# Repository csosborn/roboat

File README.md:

# Roboat!

An autonomous, solar-powered boat. An RP2040 microcontroller handles power monitoring and control and supervises a Raspberry Pi, which provides data storage, navigation, planning, and communications.

## Design documents

- [Compute.md](Compute.md): compute architecture and the power-management state machine
- [PowerSystem.md](PowerSystem.md): battery, charge controller, and solar array selection
- [SolarArrayTrade.md](SolarArrayTrade.md): solar array trade study

## Repository layout

| Path | Contents |
| --- | --- |
| `src/micro/` | MicroPython code for the RP2040 Feather (power FSM, Victron MPPT, INA260, Pi link) |
| `src/pi/` | Raspberry Pi monitor service, TIG stack (Telegraf/InfluxDB/Grafana), and systemd units; see [setup notes](src/pi/TIG/setup.md) |
| `src/build-tools/` | Docker container for building custom MicroPython firmware |
| `printed_parts/` | STL files for 3D-printed parts |
| `take1/` | The original Arduino/Eagle-based attempt, kept for reference |

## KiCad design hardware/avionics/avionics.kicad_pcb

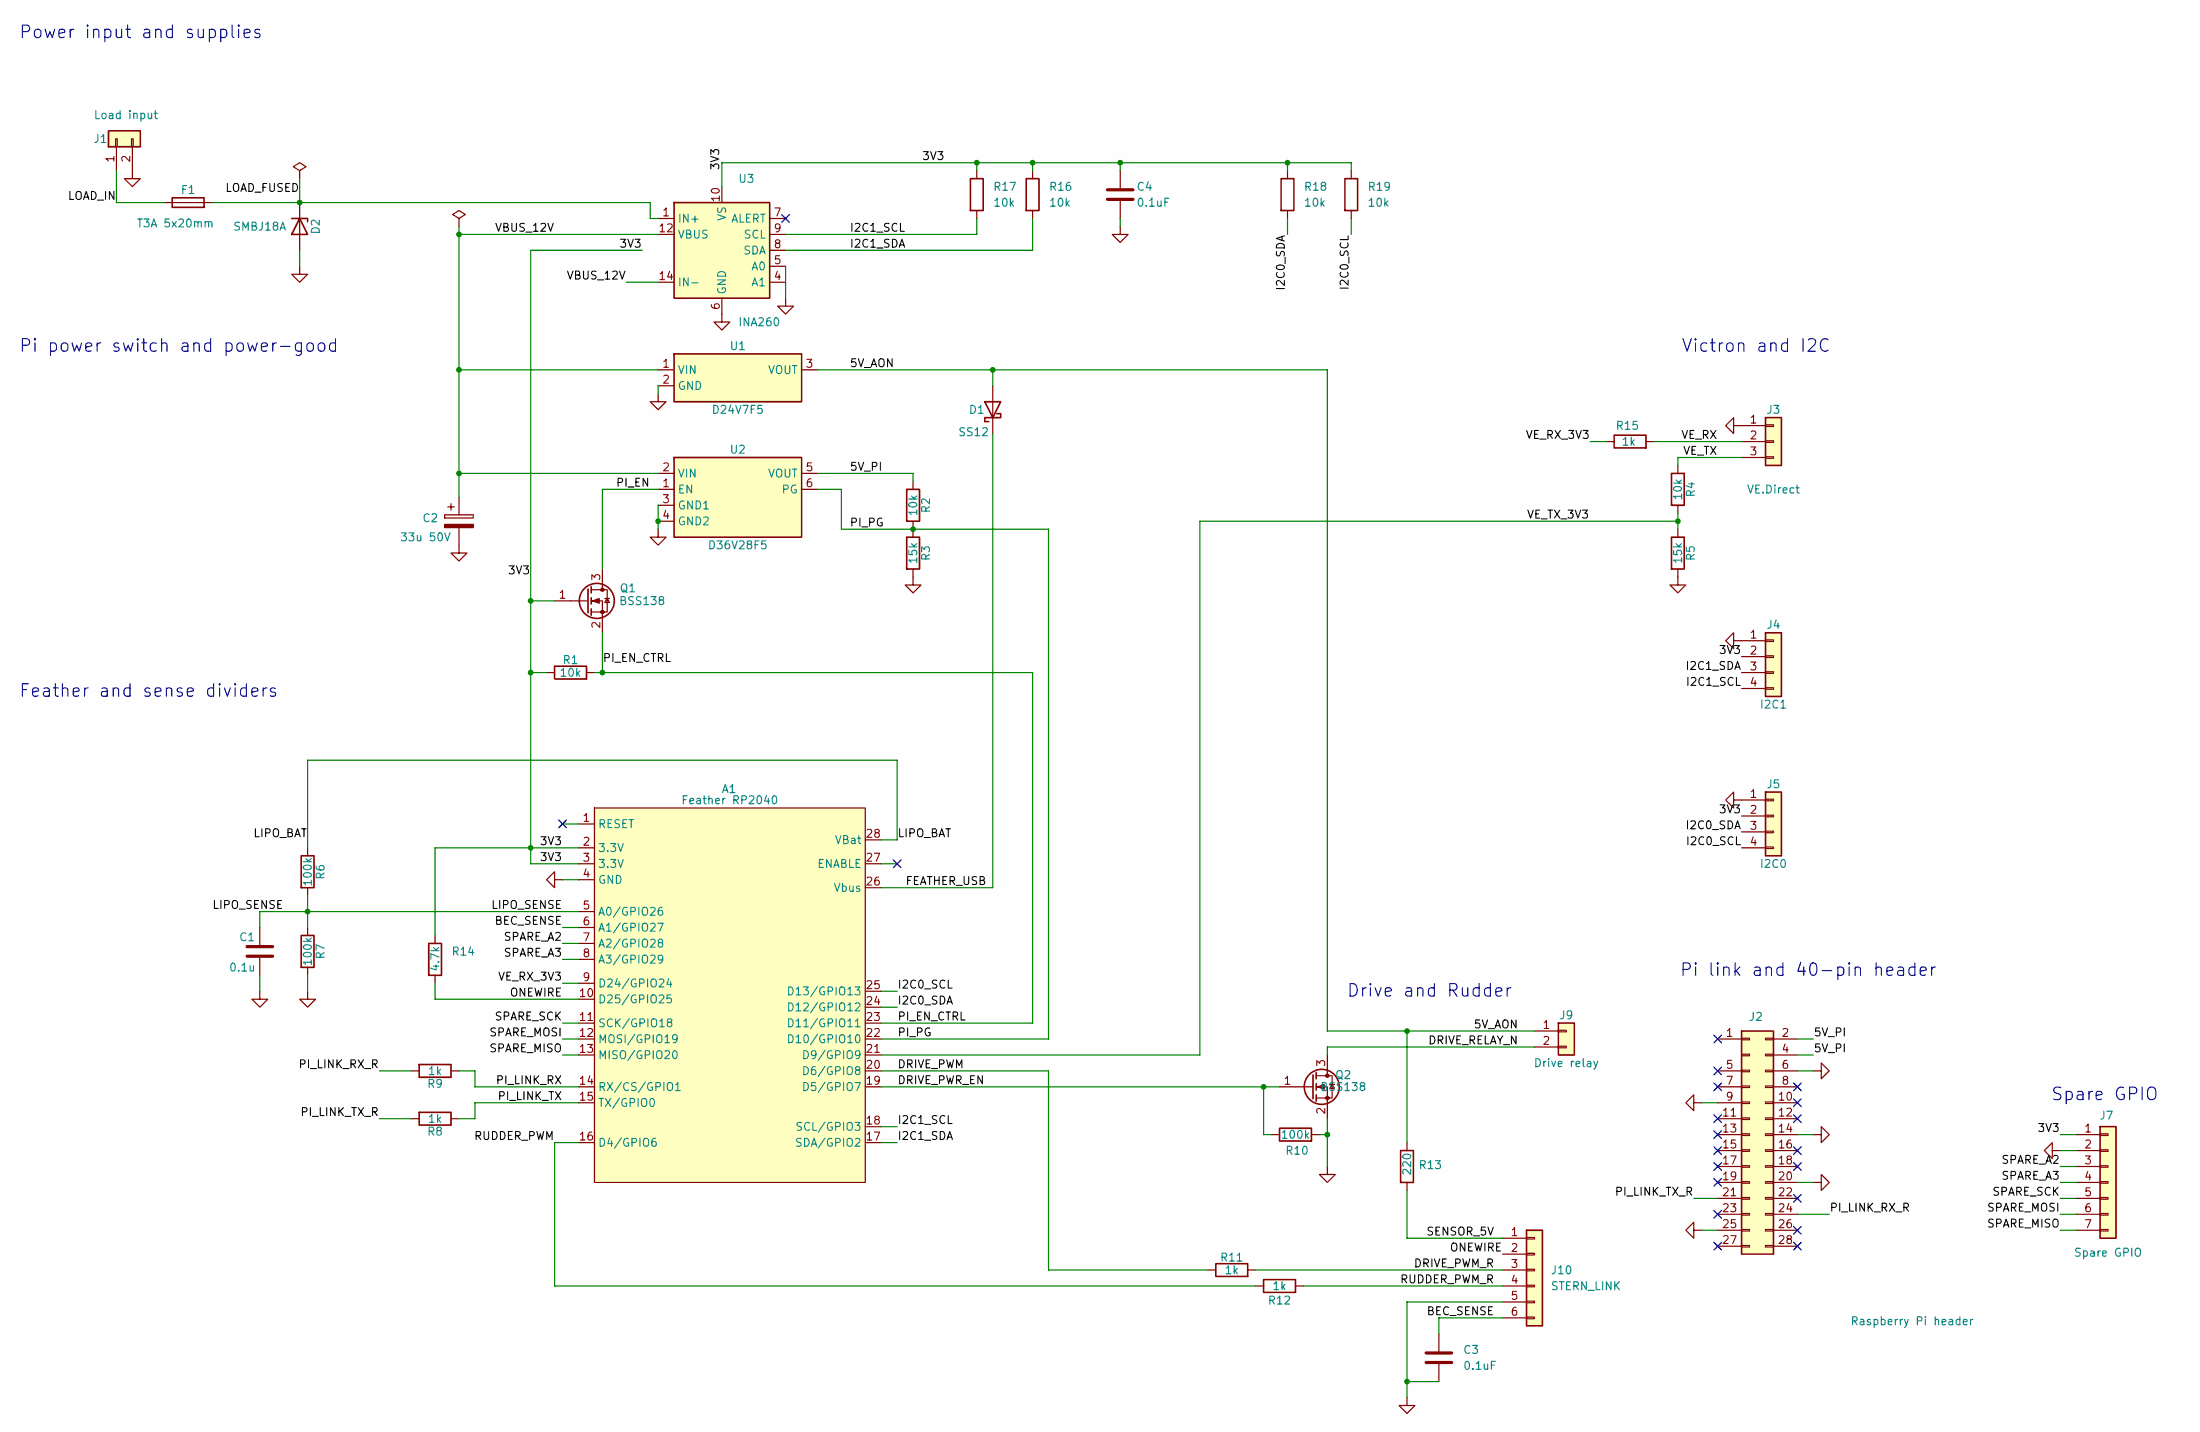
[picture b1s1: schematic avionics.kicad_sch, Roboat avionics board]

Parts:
A1: Feather RP2040; Adafruit-Feather-RP2040
C1: 0.1u; C_0402_1005Metric_Pad0.74x0.62mm_HandSolder
C2: 33u 50V; CP_Radial_D6.3mm_P2.50mm
C3, C4: 0.1uF; C_0402_1005Metric_Pad0.74x0.62mm_HandSolder
D1: SS12; D_SMA
D2: SMBJ18A; D_SMB
F1: T3A 5x20mm; Fuseholder_Clip-5x20mm_Keystone_3517_Inline_P23.11x6.76mm_D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
J1: Load input; AMASS_XT30PW-M_1x02_P2.50mm_Horizontal
J2: Raspberry Pi header; PinSocket_2x14_P2.54mm_Vertical_NoPin3
J3: VE.Direct; JST_PH_S3B-PH-K_1x03_P2.00mm_Horizontal
J4: I2C1; JST_SH_BM04B-SRSS-TB_1x04-1MP_P1.00mm_Vertical
J5: I2C0; JST_SH_BM04B-SRSS-TB_1x04-1MP_P1.00mm_Vertical
J7: Spare GPIO; PinHeader_1x07_P2.54mm_Vertical
J9: Drive relay; JST_PH_S2B-PH-K_1x02_P2.00mm_Horizontal
J10: STERN_LINK; JST_PH_S6B-PH-K_1x06_P2.00mm_Horizontal
Q1, Q2: BSS138; SOT-23
R1, R2, R4, R16, R17, R18, R19: 10k; R_0805_2012Metric
R3, R5: 15k; R_0805_2012Metric
R6, R7, R10: 100k; R_0805_2012Metric
R8, R9, R11, R12, R15: 1k; R_0805_2012Metric
R13: 220; R_1206_3216Metric
R14: 4.7k; R_0805_2012Metric
U1: D24V7F5; Pololu_D24V7F5
U2: D36V28F5; Pololu_D36V28F5
U3: INA260; TSSOP-16_4.4x5mm_P0.65mm

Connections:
/3V3: A1.2 (3.3V), A1.3 (3.3V), C4.1, J4.2, J5.2, J7.1, Q1.1 (G), R1.1, R14.1, R16.1, R17.1, R18.1, R19.1, U3.10 (VS)
/5V_AON: D1.2 (A), J9.1, R13.1, U1.3 (VOUT)
/5V_PI: J2.2, J2.4, R2.1, U2.5 (VOUT)
/BEC_SENSE: A1.6 (A1/GPIO27), C3.1, J10.6
/DRIVE_PWM: A1.20 (D6/GPIO8), R11.1
/DRIVE_PWM_R: J10.3, R11.2
/DRIVE_PWR_EN: A1.19 (D5/GPIO7), Q2.1 (G), R10.1
/DRIVE_RELAY_N: J9.2, Q2.3 (D)
/FEATHER_USB: A1.26 (Vbus), D1.1 (K)
/I2C0_SCL: A1.25 (D13/GPIO13), J5.4, R19.2
/I2C0_SDA: A1.24 (D12/GPIO12), J5.3, R18.2
/I2C1_SCL: A1.18 (SCL/GPIO3), J4.4, R17.2, U3.9 (SCL)
/I2C1_SDA: A1.17 (SDA/GPIO2), J4.3, R16.2, U3.8 (SDA)
/LIPO_BAT: A1.28 (VBat), R6.1
/LIPO_SENSE: A1.5 (A0/GPIO26), C1.1, R6.2, R7.1
/LOAD_FUSED: D2.1 (K), F1.2, U3.1 (IN+), U3.2 (IN+), U3.3 (IN+)
/LOAD_IN: F1.1, J1.1
/ONEWIRE: A1.10 (D25/GPIO25), J10.2, R14.2
/PI_EN: Q1.3 (D), U2.1 (EN)
/PI_EN_CTRL: A1.23 (D11/GPIO11), Q1.2 (S), R1.2
/PI_LINK_RX: A1.14 (RX/CS/GPIO1), R9.1
/PI_LINK_RX_R: J2.24, R9.2
/PI_LINK_TX: A1.15 (TX/GPIO0), R8.1
/PI_LINK_TX_R: J2.21, R8.2
/PI_PG: A1.22 (D10/GPIO10), R2.2, R3.1, U2.6 (PG)
/RUDDER_PWM: A1.16 (D4/GPIO6), R12.1
/RUDDER_PWM_R: J10.4, R12.2
/SENSOR_5V: J10.1, R13.2
/SPARE_A2: A1.7 (A2/GPIO28), J7.3
/SPARE_A3: A1.8 (A3/GPIO29), J7.4
/SPARE_MISO: A1.13 (MISO/GPIO20), J7.7
/SPARE_MOSI: A1.12 (MOSI/GPIO19), J7.6
/SPARE_SCK: A1.11 (SCK/GPIO18), J7.5
/VBUS_12V: C2.1, U1.1 (VIN), U2.2 (VIN), U3.12 (VBUS), U3.14 (IN-), U3.15 (IN-), U3.16 (IN-)
/VE_RX: J3.2, R15.2
/VE_RX_3V3: A1.9 (D24/GPIO24), R15.1
/VE_TX: J3.3, R4.1
/VE_TX_3V3: A1.21 (D9/GPIO9), R4.2, R5.1
GND: A1.4 (GND), C1.2, C2.2, C3.2, C4.2, D2.2 (A), J1.2, J2.6, J2.9, J2.14, J2.20, J2.25, J3.1, J4.1, J5.1, J7.2, J10.5, Q2.2 (S), R3.2, R5.2, R7.2, R10.2, U1.2 (GND), U2.3 (GND1), U2.4 (GND2), U3.4 (A1), U3.5 (A0), U3.6 (GND), U3.11 (GND)

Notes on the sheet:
Victron and I2C
Power input and supplies
Drive and Rudder
Pi power switch and power-good
Feather and sense dividers
Spare GPIO
Pi link and 40-pin header

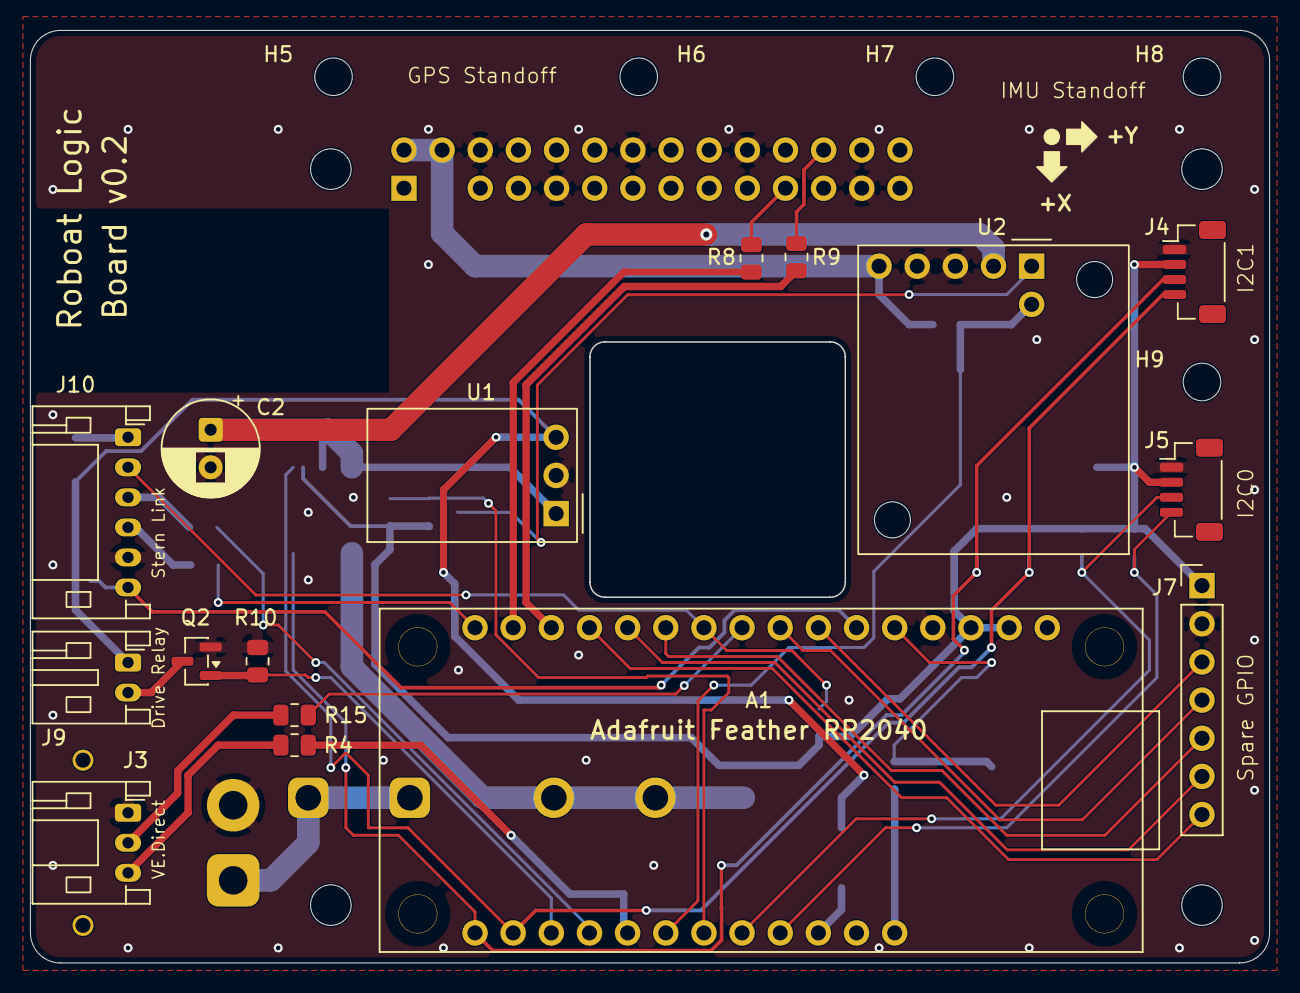
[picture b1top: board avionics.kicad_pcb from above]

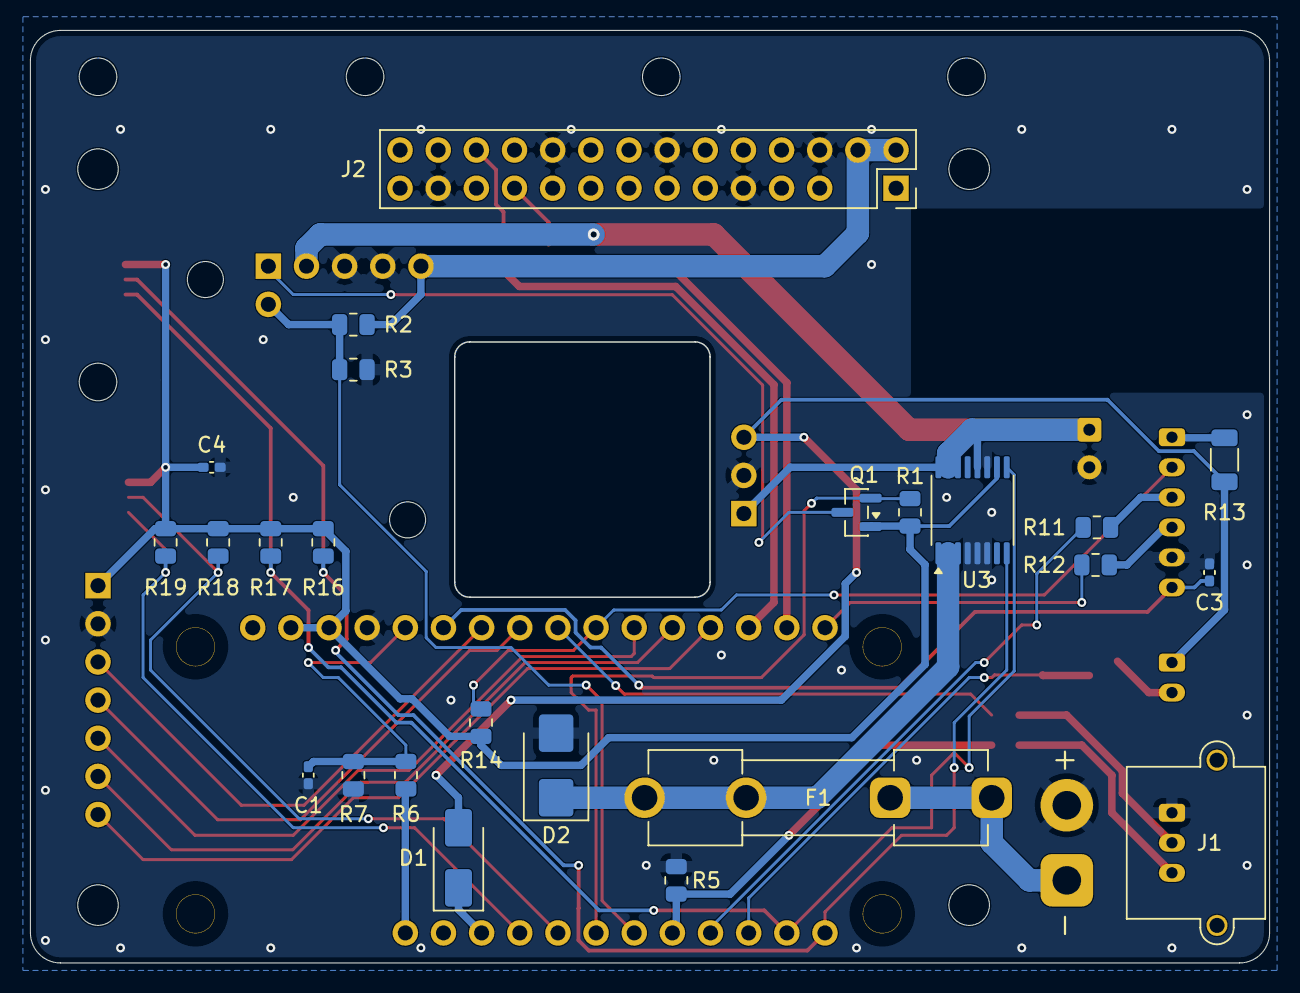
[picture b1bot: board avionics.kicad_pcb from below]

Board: 2 copper layers, 82.5 x 62.1 mm, 49 parts (24 on the bottom side), 39 nets.

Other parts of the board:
H1, H2, H3, H4: MountingHole_2.7mm_M2.5
H5, H6, H7, H8, H9: MountingHole_2.5mm

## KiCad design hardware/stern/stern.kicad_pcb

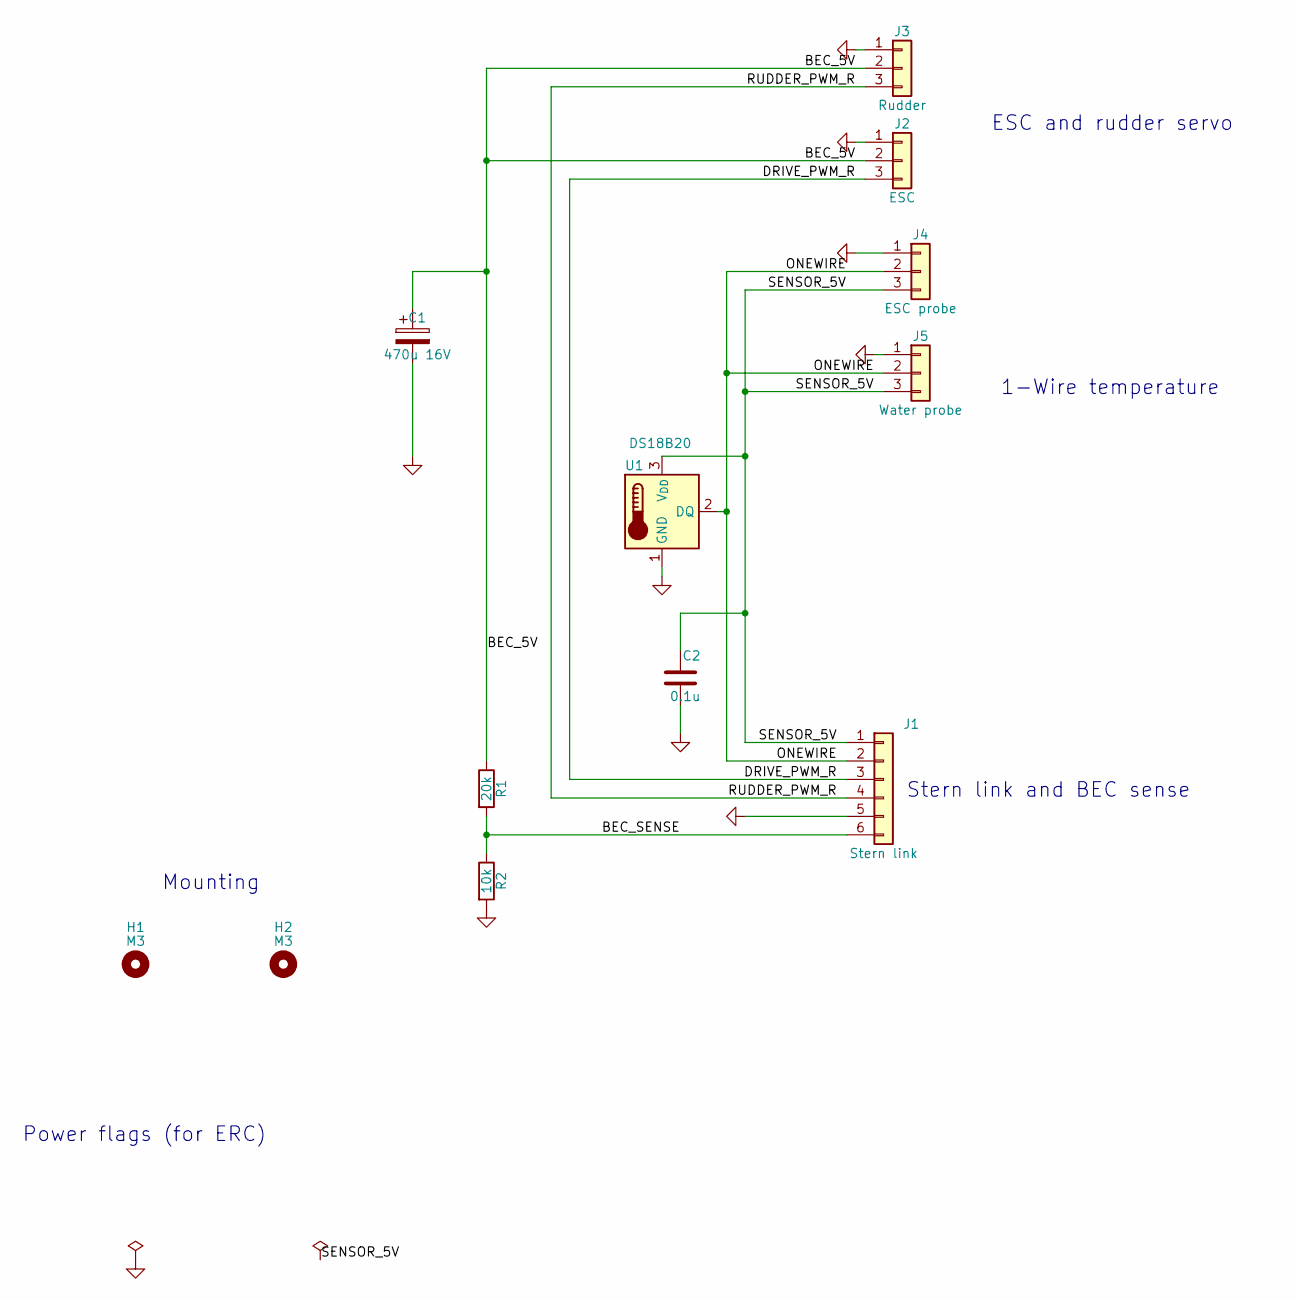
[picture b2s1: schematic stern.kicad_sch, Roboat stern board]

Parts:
C1: 470u 16V; CP_Radial_D8.0mm_P3.50mm
C2: 0.1u; C_0805_2012Metric
H1, H2: M3; MountingHole_3.2mm_M3
J1: Stern link; JST_PH_S6B-PH-K_1x06_P2.00mm_Horizontal
J2: ESC; JST_XH_S3B-XH-A_1x03_P2.50mm_Horizontal
J3: Rudder; JST_XH_S3B-XH-A_1x03_P2.50mm_Horizontal
J4: ESC probe; JST_PH_S3B-PH-K_1x03_P2.00mm_Horizontal
J5: Water probe; JST_PH_S3B-PH-K_1x03_P2.00mm_Horizontal
R1: 20k; R_0805_2012Metric
R2: 10k; R_0805_2012Metric
U1: DS18B20; TO-92_Inline

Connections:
/BEC_5V: C1.1, J2.2, J3.2, R1.1
/BEC_SENSE: J1.6, R1.2, R2.1
/DRIVE_PWM_R: J1.3, J2.3
/ONEWIRE: J1.2, J4.2, J5.2, U1.2 (DQ)
/RUDDER_PWM_R: J1.4, J3.3
/SENSOR_5V: C2.1, J1.1, J4.3, J5.3, U1.3 (V_{DD})
GND: C1.2, C2.2, J1.5, J2.1, J3.1, J4.1, J5.1, R2.2, U1.1 (GND)

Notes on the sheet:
Mounting
1-Wire temperature
ESC and rudder servo
Stern link and BEC sense
Power flags (for ERC)

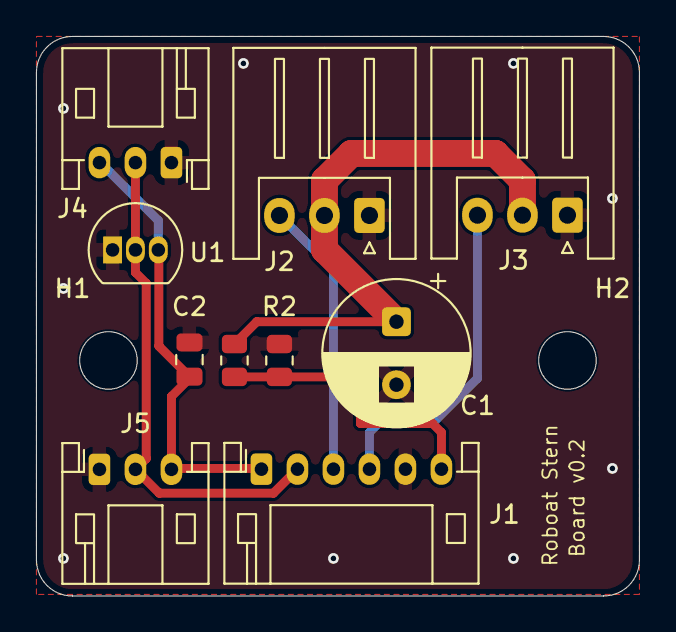
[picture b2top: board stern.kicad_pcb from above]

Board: 2 copper layers, 33.5 x 31.1 mm, 12 parts (0 on the bottom side), 7 nets.

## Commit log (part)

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2017-09-11 First commit, with notes and initial Arduino code skeleton.
2017-10-14 Tinkering with the Pilot module firmware.
2017-11-06 Added PCB and related Eagle libraries.
2017-11-06 Updated Arduino code with new pin assignments from PCB.
2017-11-13 All parts accounted for.
2017-12-23 Added initial AHRS state machine to Pilot module.
2017-12-24 Factored Roboat::StateMachine out of Roboat::AHRS.
2017-12-24 Added PowerManager state machine to Pilot module.
2017-12-26 Rearranged initializer lists to avoid reorder warnings
2018-01-02 Refactoring, cleanup, const-correctness
2018-01-08 Factored GPS code into RoboatGPSManager state machine
2018-01-08 Sketched out Captain state machine. More refactoring.
2018-01-27 Small corrections.
2019-03-03 Initial captain skeleton and connection to helm.
2019-03-04 Cleaned up CMake/Conan approach, added SQLite.
2019-03-04 Early experiments with SQLite-based persistence.
2019-03-05 Added prepared statement step() method.
2024-10-24 Move abandoned prehistory to take1 directory.
2024-10-24 Some basic notes on Roboat, take 2.
2024-10-24 Basic containerized TIG stack.
2024-10-24 Don't ignore src/pi.
2024-10-24 Initial scratch work on RP2040.
2024-10-24 Initial scratch work on Pi side.
2024-10-24 Omit Grafana pending memory upgrade.
2024-12-02 TIG stack and supporting systemd units.
2024-12-02 RP2040 micropython lib directory.
2024-12-02 RPi-based monitor program (not yet containerized)
2024-12-02 Some updated notes on the power control state machine.
2024-12-02 Grafana dashboard definition.
2024-12-02 A bunch of disorganized changes to the RP2040 code.
2024-12-14 Added micropython-builder container.
2024-12-14 Remove incorrectly added submodules.
2025-06-19 A initial quite mediocre SoC estimator.
2025-06-19 Avionics testbed and sync util.
